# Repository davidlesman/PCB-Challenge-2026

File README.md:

# UCL x KCL x Oxford x Imperial x Cambridge x Edinburgh: 2026 PCB Challenge | Sponsored by PCBWay and Jane Street

This is my entry for the PCB Challenge from the Fleming Society sponsored by PCBWay and Jane St, more information [here](https://github.com/Fleming-Society/PCB-Challenge-2026/).

The goal was to design a fully wired, single board PCB implementation of the given logic, optimized for the smallest possible board area. 
Please see below a preview of my submission, following the design constraints laid out in the repository, and the schematic.

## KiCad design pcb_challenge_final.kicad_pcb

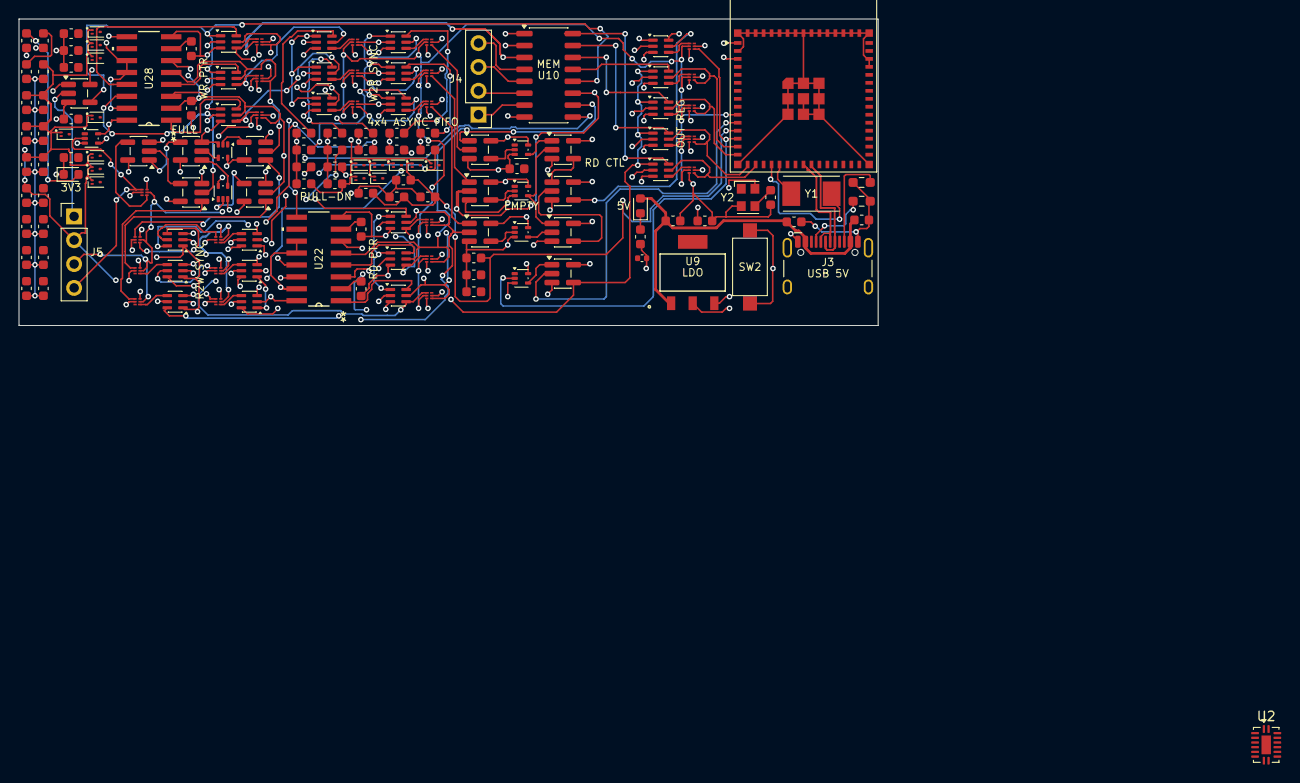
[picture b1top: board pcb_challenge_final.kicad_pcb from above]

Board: 4 copper layers, 91.5 x 32.7 mm, 154 parts (0 on the bottom side), 118 nets.

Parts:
C9: 100nF; C_0402_1005Metric
C13, C14: 1uF; C_0603_1608Metric
C15, C20: 10uF; C_0603_1608Metric
D1: BLED; LED_0603_1608Metric
GREEN_LED1: LED; LED_0603_1608Metric
J3: USB_C_Receptacle_HCTL_HC-TYPE-C-16P-01A
J4, J5: Conn_01x04_Pin; PinHeader_1x04_P2.54mm_Vertical
Q12, Q13, Q14, Q15, Q16, Q18, Q19, Q20, Q21, Q22, Q23, Q24, Q25, Q26, Q27: Q_Dual_NPN_PNP_B1E2B2C2E1C1; SOT-1123
R3: 1k; C_0603_1608Metric
R4: 330; C_0603_1608Metric
R6, R24: 1M; C_0603_1608Metric
R7, R21, R22, R23, R25, R26, R27, R28, R29, R30, R31, R32, R33, R34, R35, R36, R37, R38, R39, R40, R41, R42, R43, R44, R45, R46, R47, R48, R49, R50, R51, R52, R53, R54, R55, R56, R57, R58, R59, R61, R62, R63, R64, R65, R66, R67, R68: 10k; C_0603_1608Metric
R15, R20: 5.1k; R_0603_1608Metric_Pad0.98x0.95mm_HandSolder
SW2: SW_MEC_5G; SW_SPST_CK_RS282G05A3
U1, U4, U5, U6, U7, U8, U17, U19, U20, U33, U34, U37, U38, U45, U46, U47, U48, U49, U50, U65, U66, U67, U68, U69: 74AUP1G80; XSON6_SOT1115_NEX
U2: NMUX1308BQ; DHVQFN-16-1EP_2.5x3.5mm_P0.5mm_EP1x2mm
U3, U18, U52, U55, U56, U60: 74AHC1G86; SC-74A-5_1.55x2.9mm_P0.95mm
U9: TC1262-25; SOT-223_3MC_MCH
U10: NMUX1308BQ; SO-16_3.9x9.9mm_P1.27mm
U11, U12, U13, U14, U15, U16, U29, U30, U31, U32, U35, U36, U39, U40, U41, U42, U43, U44, U64, U70, U71, U72, U73: NMUX1308BQ; SOT-363_SC-70-6
U21, U23, U27, U51, U59, U62, U63: 74LV1T08GV; SC-74A-5_1.55x2.9mm_P0.95mm
U22, U28: CD74HC283M96; D16
U24, U26, U53, U54, U57, U58, U61: 74LVC1GU04DRL; SOT-553
U25: ESP32-S3-MINI-1; ESP32-S2-MINI-1
Y1: 32.768KHz; Crystal_SMD_Abracon_ABM7-2Pin_6.0x3.5mm
Y2: KC2520Z; Oscillator_SMD_Kyocera_KC2520Z-4Pin_2.5x2.0mm

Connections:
+3.3V: C14.1, R3.1, U1.5 (VCC), U3.5 (VCC), U4.5 (VCC), U5.5 (VCC), U6.5 (VCC), U7.5 (VCC), U8.5 (VCC), U9.3 (VO), U10.1 (V_{CC}), U11.2 (V_{CC}), U12.2 (V_{CC}), U13.2 (V_{CC}), U14.2 (V_{CC}), U15.2 (V_{CC}), U16.2 (V_{CC}), U17.5 (VCC), U18.5 (VCC), U19.5 (VCC), U20.5 (VCC), U21.5 (VCC), U22.6 (B0), U22.16 (VCC), U23.5 (VCC), U24.5 (+), U25.3 (3V3), U26.5 (+), U27.5 (VCC), U28.6 (B0), U28.16 (VCC), U29.2 (V_{CC}), U30.2 (V_{CC}), U31.2 (V_{CC}), U32.2 (V_{CC}), U33.5 (VCC), U34.5 (VCC), U35.2 (V_{CC}), U36.2 (V_{CC}), U37.5 (VCC), U38.5 (VCC), U39.2 (V_{CC}), U40.2 (V_{CC}), U41.2 (V_{CC}), U42.2 (V_{CC}), U43.2 (V_{CC}), U44.2 (V_{CC}), U45.5 (VCC), U46.5 (VCC), U47.5 (VCC), U48.5 (VCC), U49.5 (VCC), U50.5 (VCC), U51.5 (VCC), U52.5 (VCC), U53.5 (+), U54.5 (+), U55.5 (VCC), U56.5 (VCC), U57.5 (+), U58.5 (+), U59.5 (VCC), U60.5 (VCC), U61.5 (+), U62.5 (VCC), U63.5 (VCC), U64.2 (V_{CC}), U64.6 (Y1), U65.5 (VCC), U66.5 (VCC), U67.5 (VCC), U68.5 (VCC), U69.5 (VCC), U70.2 (V_{CC}), U71.2 (V_{CC}), U72.2 (V_{CC}), U73.2 (V_{CC}), Y2.4 (VCC)
+5V: C13.1, C15.1, C20.1, GREEN_LED1.2 (A), J3.A4 (VBUS), J3.A9 (VBUS), J3.B4 (VBUS), J3.B9 (VBUS), U9.1 (VI)
???: J5.4, U1.4 (~Q), U26.2
CLK: R7.2, Y2.3 (CLK)
COUT: U22.9 (COUT), U28.9 (COUT)
GND: C9.2, C13.2, C14.2, C15.2, C20.2, D1.1 (K), J3.A1 (GND), J3.A12 (GND), J3.B1 (GND), J3.B12 (GND), R4.1, R6.1, R7.1, R15.1, R20.2, R21.1, R22.1, R23.1, R24.1, R25.1, R26.1, R27.1, R28.1, R29.1, R30.1, R31.1, R32.1, R33.1, R34.1, R35.1, R36.1, R37.1, R38.1, R39.1, R40.1, R41.1, R42.1, R43.1, R44.1, R45.1, R46.1, R47.1, R48.1, R49.1, R50.1, R51.1, R52.1, R53.1, R54.1, R55.1, R56.1, R57.1, R58.1, R59.1, R61.1, R62.1, R63.1, R64.1, R65.1, R66.1, R67.1, R68.1, SW2.1 (A), SW2.2 (A), U1.3 (GND), U3.3 (GND), U4.3 (GND), U5.3 (GND), U6.3 (GND), U7.3 (GND), U8.3 (GND), U9.2 (GND), U10.2 (GND), U11.3 (GND), U12.3 (GND), U13.3 (GND), U14.3 (GND), U15.3 (GND), U16.3 (GND), U17.3 (GND), U18.3 (GND), U19.3 (GND), U20.3 (GND), U21.3 (GND), U22.8 (GND), U23.3 (GND), U24.3 (-), U25.1 (GND), U26.3 (-), U27.3 (GND), U28.8 (GND), U29.3 (GND), U30.3 (GND), U31.3 (GND), U32.3 (GND), U33.3 (GND), U34.3 (GND), U35.3 (GND), U36.3 (GND), U37.3 (GND), U38.3 (GND), U39.3 (GND), U40.3 (GND), U41.3 (GND), U42.3 (GND), U43.3 (GND), U44.3 (GND), U45.3 (GND), U46.3 (GND), U47.3 (GND), U48.3 (GND), U49.3 (GND), U50.3 (GND), U51.3 (GND), U52.3 (GND), U53.3 (-), U54.3 (-), U55.3 (GND), U56.3 (GND), U57.3 (-), U58.3 (-), U59.3 (GND), U60.3 (GND), U61.3 (-), U62.3 (GND), U63.3 (GND), U64.3 (GND), U65.3 (GND), U66.3 (GND), U67.3 (GND), U68.3 (GND), U69.3 (GND), U70.3 (GND), U71.3 (GND), U72.3 (GND), U73.3 (GND), Y2.2 (GND)
IO6: U6.2 (C), U7.2 (C), U8.2 (C), U25.10 (IO6), U45.2 (C), U46.2 (C), U47.2 (C), U48.2 (C), U49.2 (C), U50.2 (C), U65.2 (C), U66.2 (C), U67.2 (C), U68.2 (C), U69.2 (C)
IO7: U21.2 (A), U25.11 (IO7)
IO8: Q18.1 (B1_1), Q19.1 (B1_1), Q20.1 (B1_1), Q24.1 (B1_1), Q25.1 (B1_1), Q26.1 (B1_1), Q27.1 (B1_1), R35.2, R37.2, R39.2, R61.2, R63.2, R65.2, R67.2, U25.12 (IO8), U39.1 (S0), U40.1 (S0), U41.1 (S0), U42.1 (S0), U43.1 (S0), U44.1 (S0), U64.1 (S0)
IO9: U24.2, U25.13 (IO9), U65.4 (~Q)
IO10: U25.14 (IO10), U69.4 (~Q), U73.5 (Y0)
IO11: U25.15 (IO11), U68.4 (~Q), U70.5 (Y0)
IO12: U25.16 (IO12), U67.4 (~Q), U71.5 (Y0)
IO13: U25.17 (IO13), U66.4 (~Q), U72.5 (Y0)
unnamed: D1.2 (A), R3.2
unnamed: GREEN_LED1.1 (K), R4.2
unnamed: J3.A5 (CC1), R20.1
unnamed: J3.B5 (CC2), R15.2
unnamed: R6.2, R24.2
unnamed: U1.1 (D), U27.4 (Y)
unnamed: U66.1 (D), U72.4 (Out)
unnamed: U67.1 (D), U71.4 (Out)
unnamed: U68.1 (D), U70.4 (Out)
unnamed: U69.1 (D), U73.4 (Out)
unnamed: U18.4, U54.2
unnamed: U21.1 (B), U24.4
unnamed: R33.2, U22.2 (B1), U22.11 (B3), U22.12 (A3), U22.15 (B2)
unnamed: R25.2, U22.7 (CIN)
unnamed: U23.1 (B), U26.4
unnamed: U25.2 (GND), U25.42 (GND), U25.43 (GND), U25.46 (GND), U25.47 (GND), U25.48 (GND), U25.49 (GND), U25.50 (GND), U25.51 (GND), U25.52 (GND), U25.53 (GND), U25.54 (GND), U25.55 (GND), U25.56 (GND), U25.57 (GND), U25.58 (GND), U25.59 (GND), U25.60 (GND), U25.61 (GND), U25.62 (GND), U25.63 (GND), U25.64 (GND), U25.65 (GND)
unnamed: U25.19 (IO15), Y1.2
unnamed: U25.20 (IO16), Y1.1
unnamed: U3.4, U27.2 (A)
unnamed: U27.1 (B), U51.4 (Y)
unnamed: R47.2, U28.2 (B1), U28.11 (B3), U28.12 (A3), U28.15 (B2)
unnamed: R34.2, U28.7 (CIN)
unnamed: U4.1 (D), U29.4 (Out)
unnamed: R48.2, U29.6 (Y1)
unnamed: U5.1 (D), U30.4 (Out)
unnamed: U4.4 (~Q), U30.5 (Y0)
unnamed: R49.2, U30.6 (Y1)
unnamed: U31.4 (Out), U33.1 (D)
unnamed: R50.2, U31.6 (Y1)
unnamed: U32.4 (Out), U34.1 (D)
unnamed: U32.5 (Y0), U33.4 (~Q)
unnamed: R51.2, U32.6 (Y1)
unnamed: U35.4 (Out), U37.1 (D)
unnamed: R52.2, U35.6 (Y1)
unnamed: U36.4 (Out), U38.1 (D)
unnamed: U36.5 (Y0), U37.4 (~Q)
unnamed: R53.2, U36.6 (Y1)
unnamed: U39.4 (Out), U45.1 (D)
unnamed: R54.2, U39.6 (Y1)
unnamed: U40.4 (Out), U46.1 (D)
unnamed: R55.2, U40.6 (Y1)
unnamed: U41.4 (Out), U47.1 (D)
unnamed: R56.2, U41.6 (Y1)
unnamed: U42.4 (Out), U48.1 (D)
unnamed: U42.5 (Y0), U45.4 (~Q)
unnamed: R57.2, U42.6 (Y1)
unnamed: U43.4 (Out), U49.1 (D)
unnamed: U43.5 (Y0), U46.4 (~Q)
unnamed: R58.2, U43.6 (Y1)
unnamed: U44.4 (Out), U50.1 (D)
unnamed: U44.5 (Y0), U47.4 (~Q)
unnamed: R59.2, U44.6 (Y1)
unnamed: U51.2 (A), U54.4
unnamed: U51.1 (B), U53.4
unnamed: U52.4, U53.2
unnamed: U55.4, U57.2
unnamed: U56.4, U58.2
unnamed: U57.4, U59.2 (A)
unnamed: U58.4, U59.1 (B), U62.2 (A)
unnamed: U59.4 (Y), U63.2 (A)
unnamed: U60.4, U61.2
unnamed: U61.4, U62.1 (B)
unnamed: U62.4 (Y), U63.1 (B)
unnamed: U63.4 (Y), U64.5 (Y0)
unnamed: U64.4 (Out), U65.1 (D)
R_en: U10.12 (EN), U14.1 (S0), U15.1 (S0), U16.1 (S0), U23.4 (Y)
USB_D+: J3.A6 (D+), J3.B6 (D+), U25.24 (USB_D+)
USB_D-: J3.A7 (D-), J3.B7 (D-), U25.23 (USB_D-)
b1: J4.4, U10.4 (in1)
b2: J4.3, U10.5 (in2)
b3: J4.2, U10.6 (in3)
b4: J4.1, U10.7 (in4)
clk: J5.3, U1.2 (C), U4.2 (C), U5.2 (C), U10.3 (clk), U17.2 (C), U19.2 (C), U20.2 (C), U33.2 (C), U34.2 (C), U37.2 (C), U38.2 (C)
en: J5.1, U23.2 (A)
out_1: U10.13 (o1), U73.6 (Y1)
out_2: U10.14 (o2), U70.6 (Y1)
out_3: U10.15 (o3), U71.6 (Y1)
out_4: U10.16 (o4), U72.6 (Y1)
r_en: U11.1 (S0), U12.1 (S0), U13.1 (S0), U21.4 (Y), U70.1 (S0), U71.1 (S0), U72.1 (S0), U73.1 (S0)
rc1: U7.4 (~Q), U10.10 (in1), U12.5 (Y0), U22.5 (A0), U60.1
rc2: U6.4 (~Q), U10.11 (in2), U11.5 (Y0), U22.3 (A1), U56.2
rc3: U8.4 (~Q), U13.5 (Y0), U22.14 (A2), U55.2
reg1: U5.4 (~Q), U18.1
reg2: U34.4 (~Q), U52.1
reg3: U3.1, U38.4 (~Q)
rs0: U12.6 (Y1), U22.4 (S0)
rs1: U11.6 (Y1), U22.1 (S1)
rs2: U13.6 (Y1), U22.13 (S2)
rst: J5.2, Q12.1 (B1_1), Q13.1 (B1_1), Q14.1 (B1_1), Q15.1 (B1_1), Q16.1 (B1_1), Q21.1 (B1_1), Q22.1 (B1_1), Q23.1 (B1_1), R21.2, R23.2, R27.2, R29.2, R31.2, R41.2, R42.2, R43.2, U29.1 (S0), U30.1 (S0), U31.1 (S0), U32.1 (S0), U35.1 (S0), U36.1 (S0)
rw1: U7.1 (D), U12.4 (Out), U29.5 (Y0)
rw2: U6.1 (D), U11.4 (Out), U31.5 (Y0)
rw3: U8.1 (D), U13.4 (Out), U35.5 (Y0)
wc1: U10.8 (in1), U15.5 (Y0), U18.2, U20.4 (~Q), U28.5 (A0)
wc2: U10.9 (in2), U14.5 (Y0), U19.4 (~Q), U28.3 (A1), U52.2
wc3: U3.2, U16.5 (Y0), U17.4 (~Q), U28.14 (A2)
wir1: U48.4 (~Q), U60.2
wir2: U49.4 (~Q), U56.1
wir3: U50.4 (~Q), U55.1
wr1: U15.4 (Out), U20.1 (D), U39.5 (Y0)
wr2: U14.4 (Out), U19.1 (D), U40.5 (Y0)
wr3: U16.4 (Out), U17.1 (D), U41.5 (Y0)
ws0: U15.6 (Y1), U28.4 (S0)
ws1: U14.6 (Y1), U28.1 (S1)
ws2: U16.6 (Y1), U28.13 (S2)
